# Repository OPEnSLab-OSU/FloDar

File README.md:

# FloDar | [Updates](https://github.com/OPEnSLab-OSU/OPEnS-Lab-Home/wiki/FloDar-updates) | [Wiki](https://github.com/OPEnSLab-OSU/OPEnS-Lab-Home/wiki/FloDar)

Project Lead: Cara Walter

This repository contains software, hardware, and documentation for FloDar.

See our [Wiki](https://github.com/OPEnSLab-OSU/OPEnS-Lab-Home/wiki/FloDar) for more information!

Project contact: Cara Walter (cara.walter@oregonstate.edu)

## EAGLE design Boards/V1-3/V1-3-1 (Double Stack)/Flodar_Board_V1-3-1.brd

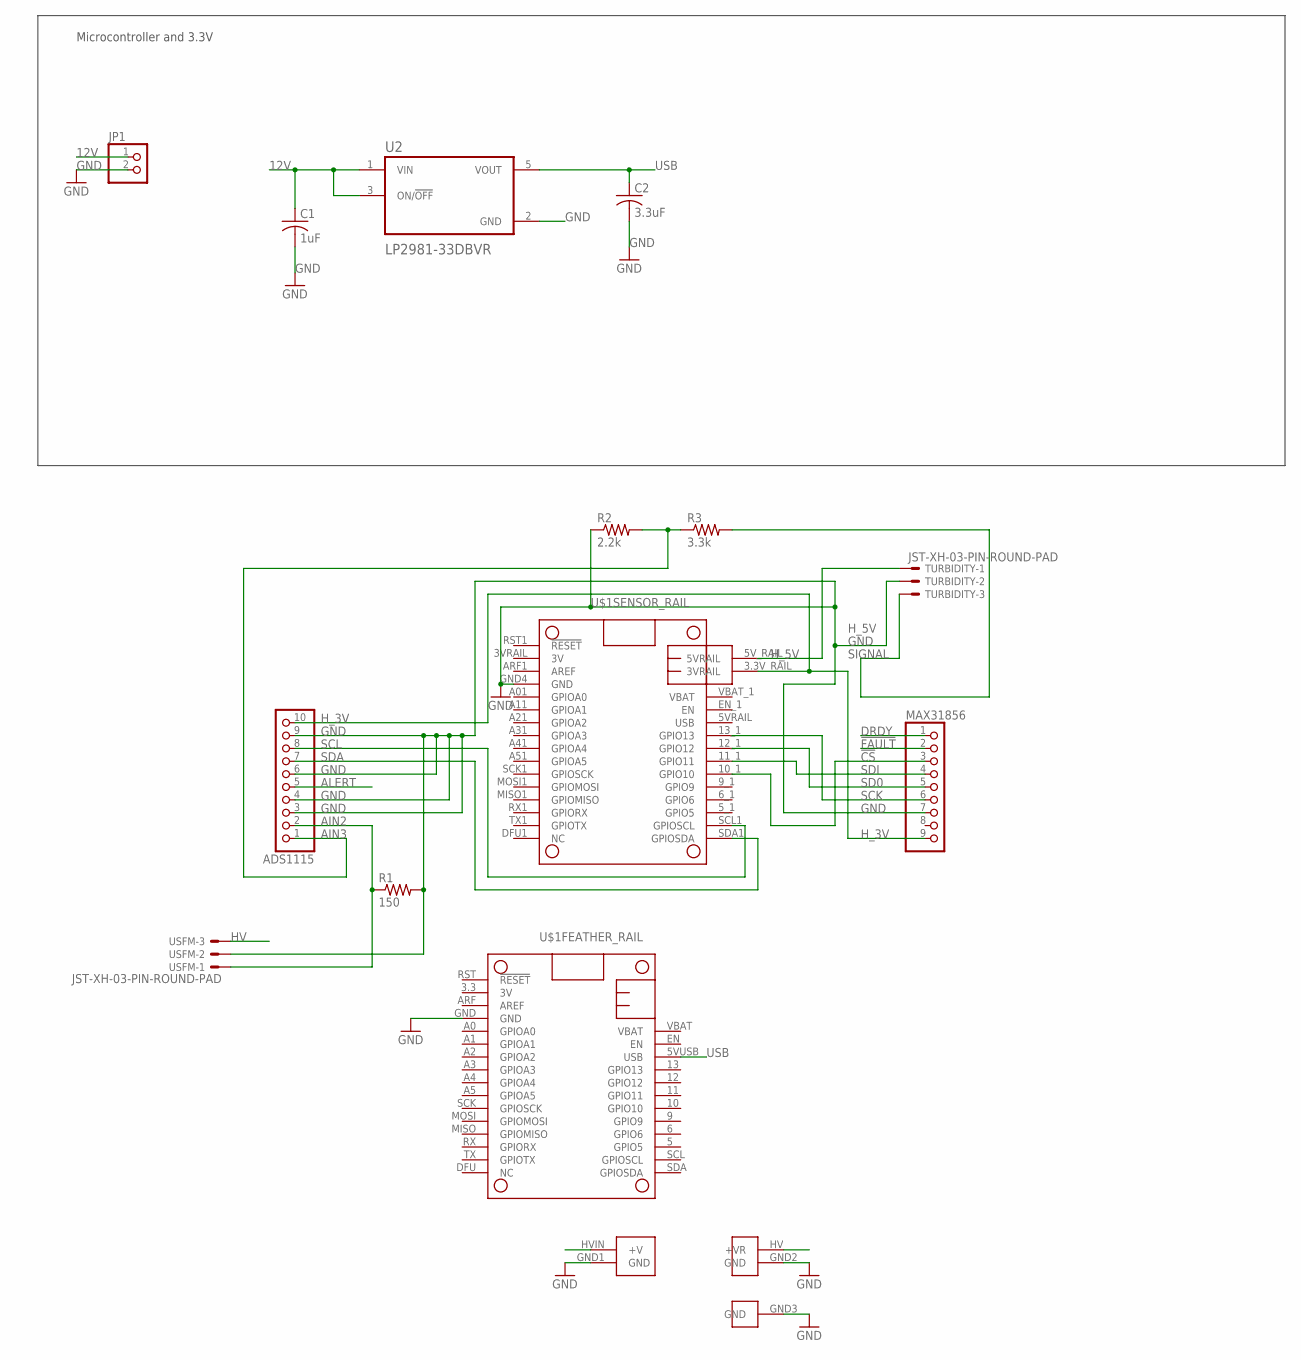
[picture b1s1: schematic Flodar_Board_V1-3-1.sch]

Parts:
ADS1115: HEADER-1X1070MIL; 1X10_ROUND70
C1: 1uF; C1206
C2: 3.3uF; C1206
JP1: PINHD-1X2; 1X02
MAX31856: HEADER-1X970MIL; 1X09_ROUND_70
R1: 150; R1206
R2: 2.2k; R1206
R3: 3.3k; R1206
TURBIDITY: JST-XH-03-PIN-ROUND-PAD; JST-XH-03-PACKAGE-ROUND-PAD
U2: LP2981-33DBVR; SOT95P280X145-5N
U$1: HYPNOS_V3
USFM: JST-XH-03-PIN-ROUND-PAD; JST-XH-03-PACKAGE-ROUND-PAD

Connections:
12V: C1.1, JP1.1, U2.1 (VIN), U2.3 (ON/!OFF), U$1.HVIN (+V)
!CS: MAX31856.3, U$1.10_1 (GPIO10)
!FAULT: MAX31856.2
AIN2: ADS1115.2, R1.1, USFM.1
AIN3: ADS1115.1, R2.2, R3.1
ALERT: ADS1115.5
DRDY: MAX31856.1
GND: ADS1115.3, ADS1115.4, ADS1115.6, ADS1115.9, C1.2, C2.2, JP1.2, MAX31856.7, R1.2, R2.1, TURBIDITY.2, U2.2 (GND), U$1.GND, U$1.GND1 (GND), U$1.GND2 (GND), U$1.GND3 (GND), U$1.GND4 (GND), USFM.2
HV: U$1.HV (+VR), USFM.3
H_3V: ADS1115.10, MAX31856.9, U$1.3.3V_RAIL (3VRAIL)
H_5V: TURBIDITY.1, U$1.5V_RAIL (5VRAIL)
SCK: MAX31856.6, U$1.13_1 (GPIO13)
SCL: ADS1115.8, U$1.SCL1 (GPIOSCL)
SD0: MAX31856.5, U$1.12_1 (GPIO12)
SDA: ADS1115.7, U$1.SDA1 (GPIOSDA)
SDI: MAX31856.4, U$1.11_1 (GPIO11)
SIGNAL: R3.2, TURBIDITY.3
USB: C2.1, U2.5 (VOUT), U$1.5VUSB (USB)

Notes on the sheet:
Microcontroller and 3.3V

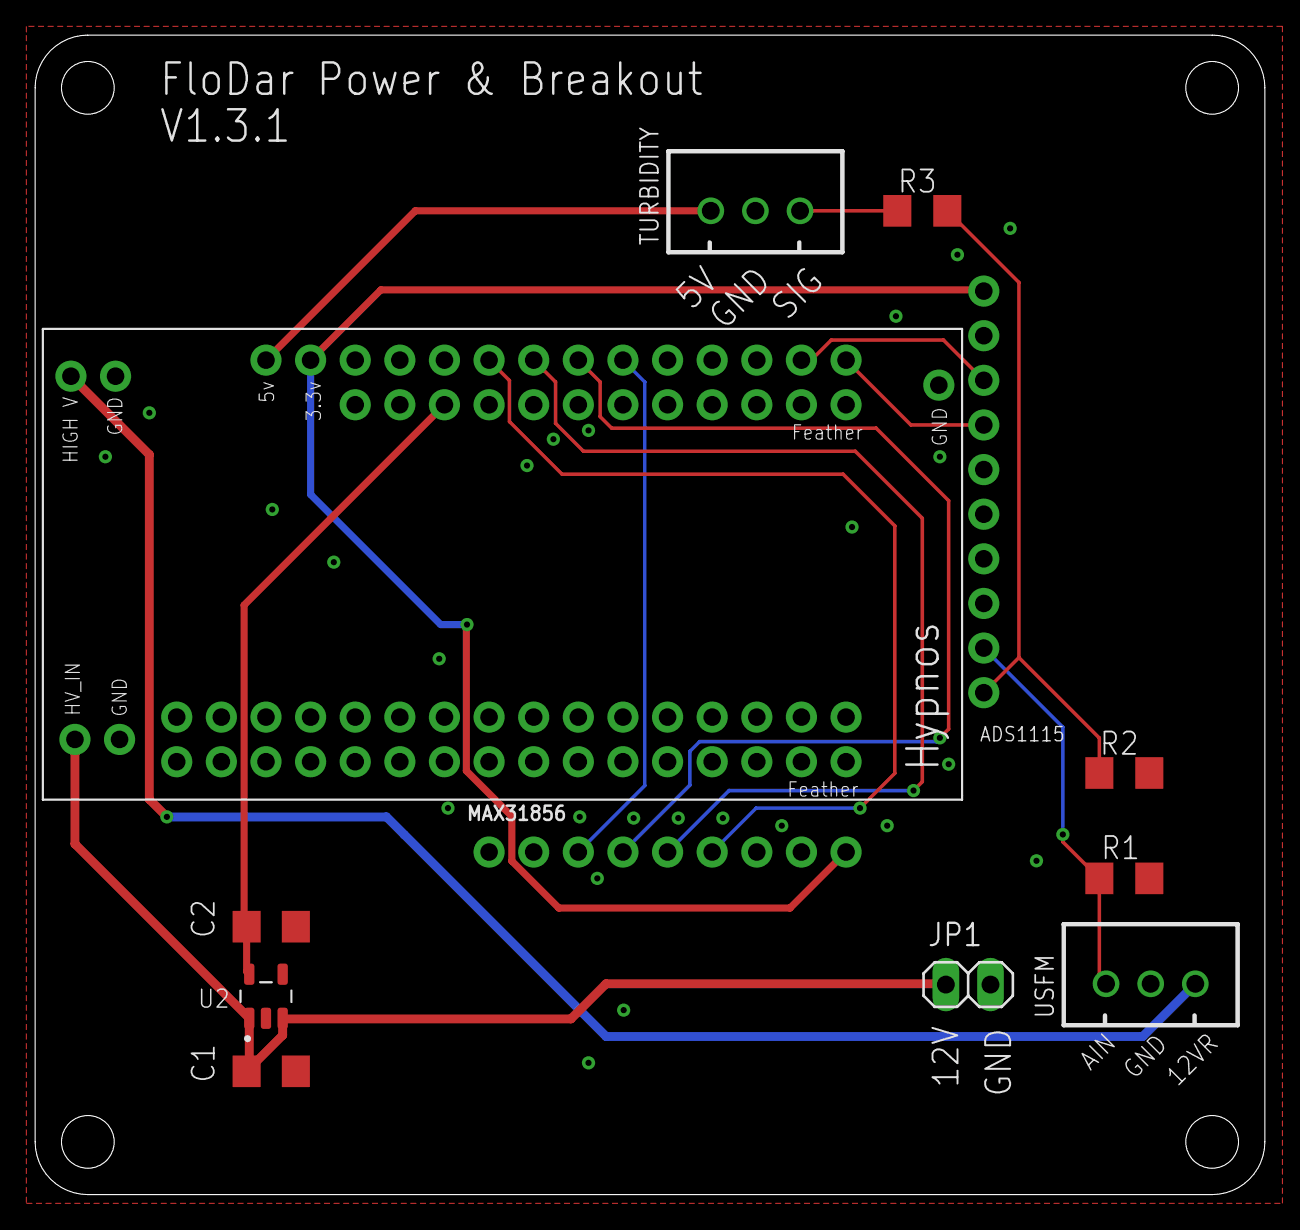
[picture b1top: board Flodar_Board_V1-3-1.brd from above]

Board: 2 copper layers, 70.0 x 66.0 mm, 12 parts (0 on the bottom side), 15 nets.

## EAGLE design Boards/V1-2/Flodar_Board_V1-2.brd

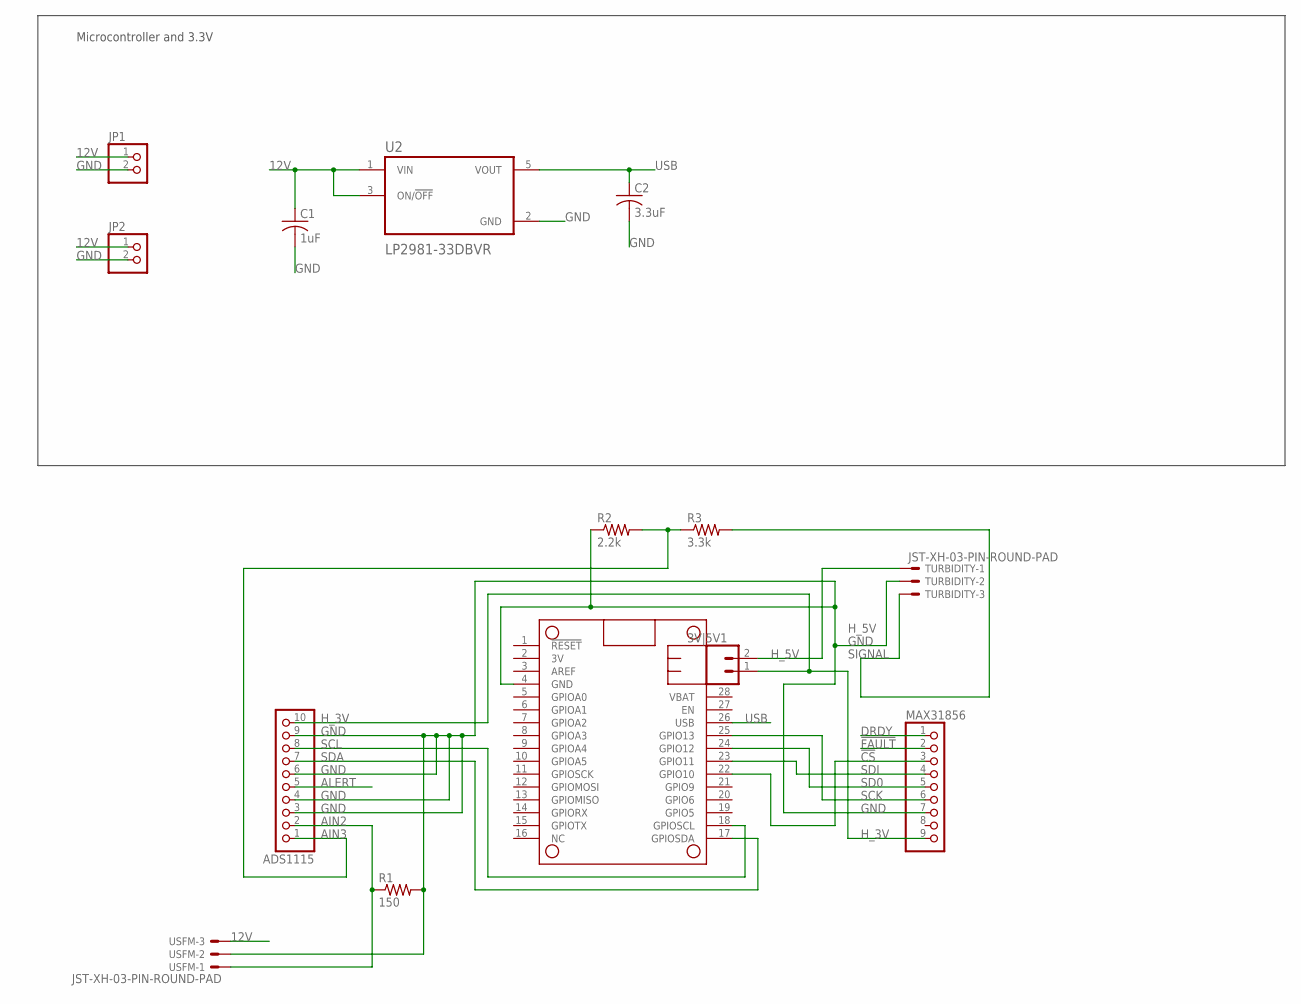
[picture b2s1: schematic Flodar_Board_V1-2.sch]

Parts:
3V|5V1: CONN_021X02_NO_SILK; 1X02_NO_SILK
ADS1115: HEADER-1X1070MIL; 1X10_ROUND70
C1: 1uF; C1206
C2: 3.3uF; C1206
JP1, JP2: PINHD-1X2; 1X02
MAX31856: HEADER-1X970MIL; 1X09_ROUND_70
MS3: FEATHERWING
R1: 150; R1206
R2: 2.2k; R1206
R3: 3.3k; R1206
TURBIDITY: JST-XH-03-PIN-ROUND-PAD; JST-XH-03-PACKAGE-ROUND-PAD
U2: LP2981-33DBVR; SOT95P280X145-5N
USFM: JST-XH-03-PIN-ROUND-PAD; JST-XH-03-PACKAGE-ROUND-PAD

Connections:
12V: C1.1, JP1.1, JP2.1, U2.1 (VIN), U2.3 (ON/!OFF), USFM.3
!CS: MAX31856.3, MS3.22 (GPIO10)
!FAULT: MAX31856.2
AIN2: ADS1115.2, R1.1, USFM.1
AIN3: ADS1115.1, R2.2, R3.1
ALERT: ADS1115.5
DRDY: MAX31856.1
GND: ADS1115.3, ADS1115.4, ADS1115.6, ADS1115.9, C1.2, C2.2, JP1.2, JP2.2, MAX31856.7, MS3.4 (GND), R1.2, R2.1, TURBIDITY.2, U2.2 (GND), USFM.2
H_3V: 3V|5V1.1, ADS1115.10, MAX31856.9
H_5V: 3V|5V1.2, TURBIDITY.1
SCK: MAX31856.6, MS3.25 (GPIO13)
SCL: ADS1115.8, MS3.18 (GPIOSCL)
SD0: MAX31856.5, MS3.24 (GPIO12)
SDA: ADS1115.7, MS3.17 (GPIOSDA)
SDI: MAX31856.4, MS3.23 (GPIO11)
SIGNAL: R3.2, TURBIDITY.3
USB: C2.1, MS3.26 (USB), U2.5 (VOUT)

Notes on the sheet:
Microcontroller and 3.3V

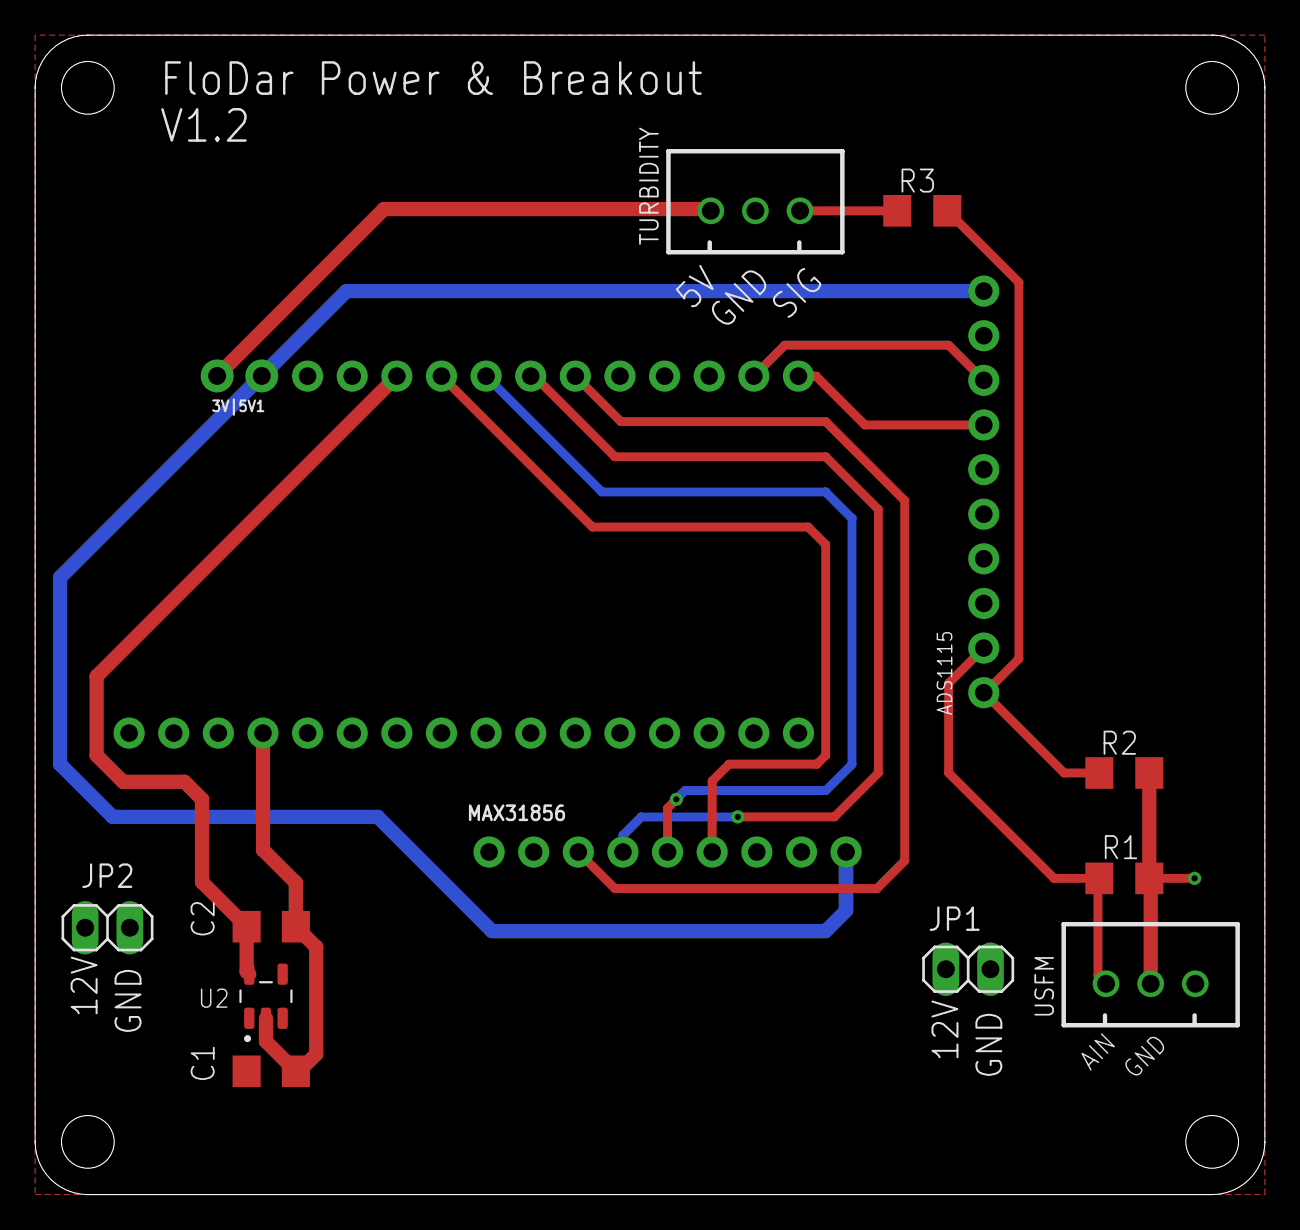
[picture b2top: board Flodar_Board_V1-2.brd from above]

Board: 2 copper layers, 70.0 x 66.0 mm, 14 parts (0 on the bottom side), 14 nets.

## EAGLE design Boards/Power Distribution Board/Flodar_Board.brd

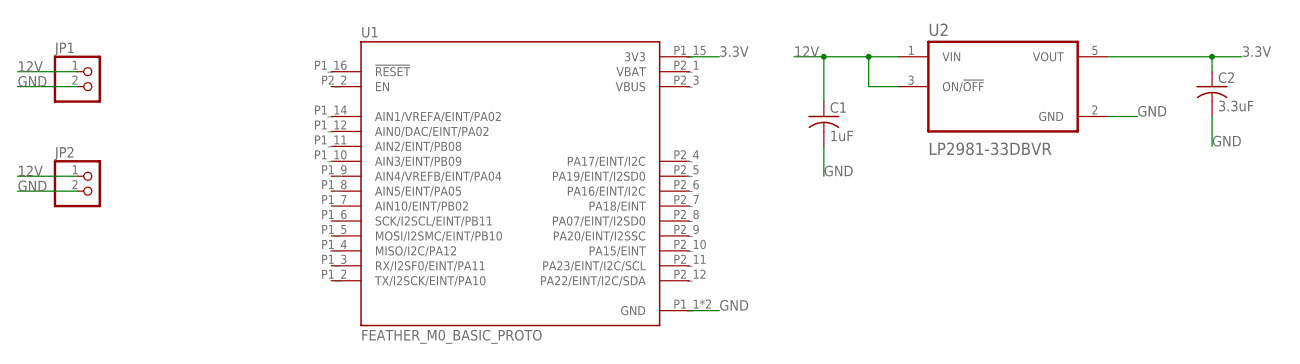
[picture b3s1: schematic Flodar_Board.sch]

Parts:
C1: 1uF; C1206
C2: 3.3uF; C1206
JP1, JP2: PINHD-1X2; 1X02
U1: FEATHER_M0_BASIC_PROTO; MODULE_FEATHER_M0_BASIC_PROTO
U2: LP2981-33DBVR; SOT95P280X145-5N

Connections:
3.3V: C2.1, U1.P1_15 (3V3), U2.5 (VOUT)
12V: C1.1, JP1.1, JP2.1, U2.1 (VIN), U2.3 (ON/!OFF)
GND: C1.2, C2.2, JP1.2, JP2.2, U1.P1_1 (GND), U1.P1_13 (GND), U2.2 (GND)
VBAT: U1.P2_1 (VBAT)
VBUS: U1.P2_3 (VBUS)

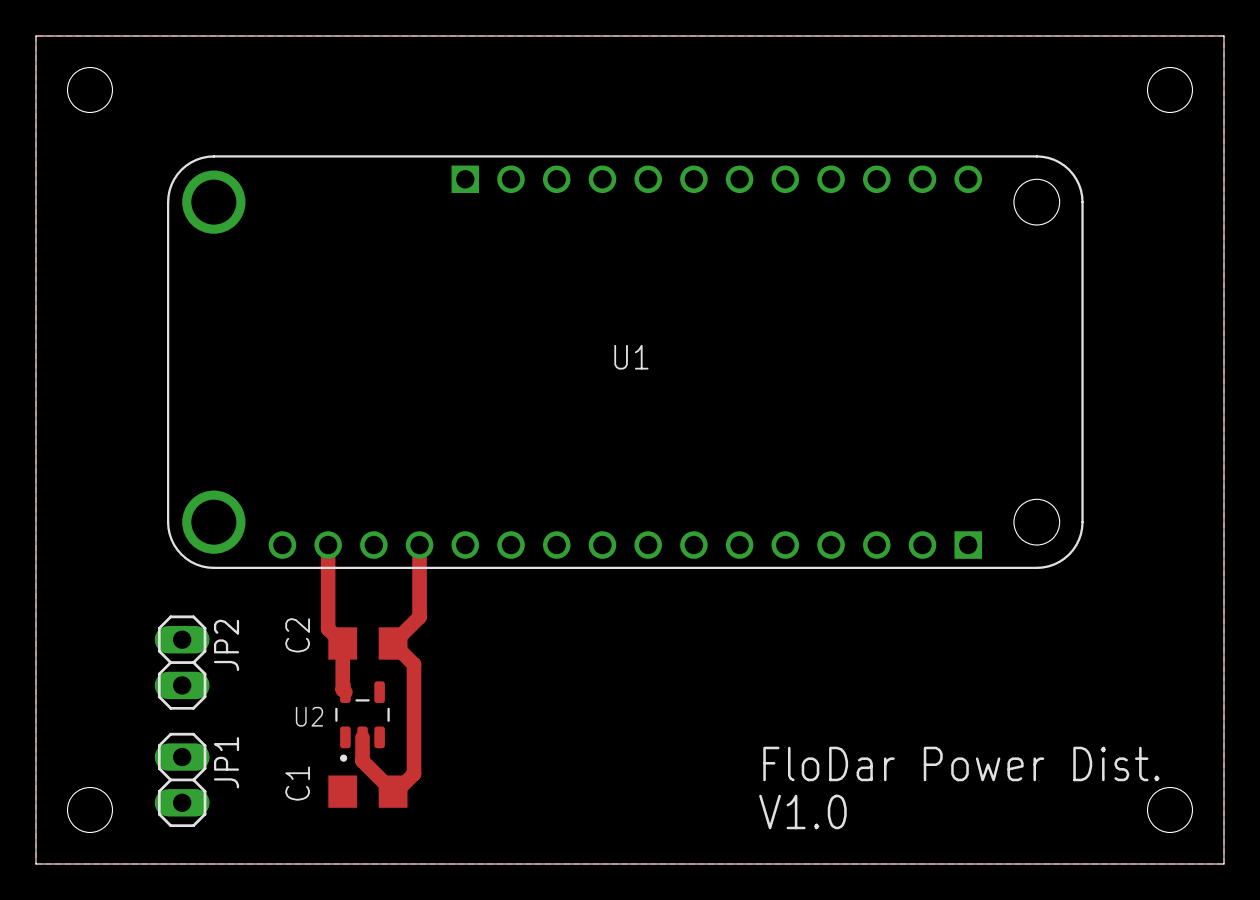
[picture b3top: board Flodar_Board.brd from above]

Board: 2 copper layers, 66.0 x 46.0 mm, 6 parts (0 on the bottom side), 3 nets.

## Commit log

2021-02-16 Upload Borads
2021-02-16 Upload Arduino Sketch
2021-03-05 System Diagram Images
2021-03-05 Add More Images
2021-05-03 Move Poster
2021-05-04 Create Black Box Diagram
2021-05-04 Add FloDar Renders
2021-06-06 Update Circuit Diagrams
2021-06-06 Power Budget Diagram
2021-06-07 Save Draw.io Diagrams
2021-07-29 Add Power Dist. Board
2021-07-30 Update Power Dist. Board
2021-08-19 Combine Breakout and Power Dist. Boards
2021-08-24 Add Labels to Pins
2021-08-31 Fix Board Dimention
2021-09-28 Upload V1-2
2021-09-28 Update Board V1-2
2021-09-28 Update Circuit Diagram
2021-09-30 Upload Summer Data
2021-10-01 Upload Board V1.3.x
2021-10-01 Pelican Structure CAD
2022-01-23 Change time interval to 15 minutes
2022-02-15 Create 30 Second Script
2022-02-15 Create Blank Script
2022-02-15 Create Test Script
2022-02-26 Update Circuit Diagram PNG
2022-03-14 Use custom DS3231 params
    change
    'params':'default'\
    to
    'params':[11, false, true]\
2022-04-23 Create Joe Script
2022-05-04 Fix typo
2022-07-14 Make Loom v2.5 and v4 folders
2022-07-14 Loom 4 Version
2022-07-14 Disable MAX31856
    MAX31856 is currently unused
2022-07-14 Add 30sec and 10sec Scripts
2022-07-14 Update FloDar.ino
    Add battery voltage reading and logging
2022-07-14 Update FloDar_10sec.ino
    Add battery voltage read and log
2022-07-14 Update FloDar_30sec.ino
    Add battery voltage and logging
2022-07-14 Move sleep duration to top of code
2022-07-16 Move BLANK script
2022-07-16 Add delay before measure
2022-07-17 Added FloDar code with the ability to add calculations to the log file
2022-07-18 Modified CustomCalc
2022-07-18 Replace FloDar with FloDar_Field
2022-07-18 Replace FloDar_xxsec with FloDar_Lab
2022-07-18 Removing delay time from alarm timing
2022-07-18 Removing unused files
2022-07-18 Update calculation
2022-07-18 Have alarm time set before loop is executed
2022-07-18 Change calculation
2022-07-19 Create barebones file
2022-07-19 Rename to testing
2022-07-19 Remade to use manager.pause()
2022-07-20 Maybe fixed drift
2022-07-27 Changing to 30 seconds
2022-07-28 Updating field code
2022-08-08 Clarifying logic
2022-10-14 Grouped solar board files and added gerber for current pcb
2022-10-14 Added feather and transducers
2022-12-01 Updated field code to match loom 4.1 ADS1115 manager
2023-03-01 Updated contact
2023-03-06 Added manual, updated system diagram
2023-03-06 Added user manual
2023-03-14 added explanation for max bits
2023-03-30 Updated CAD files
2023-03-31 No sleeping
2023-03-31 Replaced manual with one more consistent with system.
2023-06-01 Updated insert files
2023-06-05 Updated insert for battery slot
2023-09-25 Added BOM and build guide

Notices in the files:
parts and their libraries:
microbuilder: This work is placed in the public domain, and may be freely used for commercial and non-commercial work with the following conditions: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
SparkFun-Connectors: Licensing: Creative Commons ShareAlike 4.0 International - https://creativecommons.org/licenses/by-sa/4.0
